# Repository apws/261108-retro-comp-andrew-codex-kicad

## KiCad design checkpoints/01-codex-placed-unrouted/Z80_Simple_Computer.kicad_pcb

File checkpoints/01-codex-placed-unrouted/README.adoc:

= Codex placed, unrouted checkpoint

Preserve these files as the common input for routing comparisons. `checkpoint.json` records their hashes. Open `Z80_Simple_Computer.kicad_pro` to inspect the native snapshot. Signal routing is absent; two inner power planes are filled. Do not edit this checkpoint; copy it into the chosen experiment first.

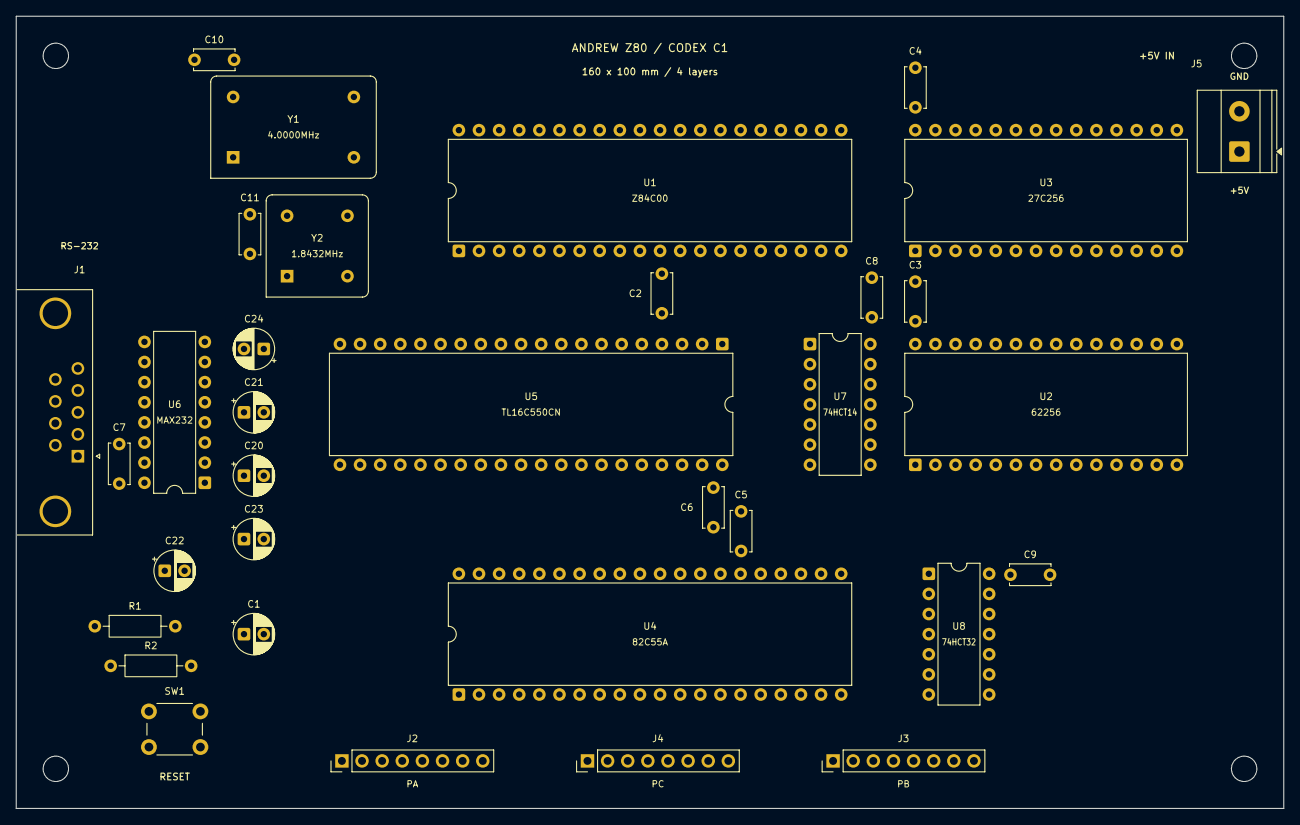
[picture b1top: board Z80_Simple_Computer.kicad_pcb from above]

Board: 4 copper layers, 160.0 x 100.0 mm, 38 parts (0 on the bottom side), 81 nets, no tracks yet.

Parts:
C1: 1uF / 16V; CP_Radial_D5.0mm_P2.50mm
C2, C3, C4, C5, C6, C7, C8, C9, C10, C11: 100nF; C_Disc_D5.0mm_W2.5mm_P5.00mm
C20, C21, C22, C23, C24: 1uF / 25V; CP_Radial_D5.0mm_P2.50mm
H1, H2, H3, H4: M3; MountingHole_3.2mm_M3
J1: RS-232 (DTE pins); DSUB-9_Socket_Horizontal_P2.77x2.84mm_EdgePinOffset4.94mm_H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
J2: PA; PinHeader_1x08_P2.54mm_Vertical
J3: PB; PinHeader_1x08_P2.54mm_Vertical
J4: PC; PinHeader_1x08_P2.54mm_Vertical
J5: +5V INPUT; TerminalBlock_Phoenix_MKDS-1,5-2-5.08_1x02_P5.08mm_Horizont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
R1: 10k; R_Axial_DIN0207_L6.3mm_D2.5mm_P10.16mm_Horizontal
R2: 10; R_Axial_DIN0207_L6.3mm_D2.5mm_P10.16mm_Horizontal
SW1: RESET; SW_PUSH_6mm
U1: Z84C00; DIP-40_W15.24mm
U2: 62256; DIP-28_W15.24mm
U3: 27C256; DIP-28_W15.24mm
U4: 82C55A; DIP-40_W15.24mm
U5: TL16C550CN; DIP-40_W15.24mm
U6: MAX232; DIP-16_W7.62mm
U7: 74HCT14; DIP-14_W7.62mm
U8: 74HCT32; DIP-14_W7.62mm
Y1: 4.0000MHz; Oscillator_DIP-14
Y2: 1.8432MHz; Oscillator_DIP-8

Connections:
+5V: C2.1, C3.1, C4.1, C5.1, C6.1, C7.1, C8.1, C9.1, C10.1, C11.1, C22.1, J5.1, R1.1, U1.11 (V_{CC}), U1.16 (~INT), U1.17 (~NMI), U1.24 (~WAIT), U1.25 (~BUSREQ), U2.28 (VCC), U3.1 (VPP), U3.28 (VCC), U4.26 (VCC), U5.12 (CS0), U5.13 (CS1), U5.38 (~DCD), U5.39 (~RI), U5.40 (VCC), U6.16 (VCC), U7.14 (VCC), U8.14 (VCC), Y1.1 (EN), Y1.14 (Vcc), Y2.1 (EN), Y2.8 (Vcc)
/A0: U1.30 (A_{0}), U2.10 (A0), U3.10 (A0), U4.9 (A0), U5.28 (A0)
/A1: U1.31 (A_{1}), U2.9 (A1), U3.9 (A1), U4.8 (A1), U5.27 (A1)
/A2: U1.32 (A_{2}), U2.8 (A2), U3.8 (A2), U5.26 (A2)
/A3: U1.33 (A_{3}), U2.7 (A3), U3.7 (A3)
/A4: U1.34 (A_{4}), U2.6 (A4), U3.6 (A4)
/A5: U1.35 (A_{5}), U2.5 (A5), U3.5 (A5)
/A6: U1.36 (A_{6}), U2.4 (A6), U3.4 (A6)
/A7: U1.37 (A_{7}), U2.3 (A7), U3.3 (A7), U7.5, U8.2
/A8: U1.38 (A_{8}), U2.25 (A8), U3.25 (A8)
/A9: U1.39 (A_{9}), U2.24 (A9), U3.24 (A9)
/A10: U1.40 (A_{10}), U2.21 (A10), U3.21 (A10)
/A11: U1.1 (A_{11}), U2.23 (A11), U3.23 (A11)
/A12: U1.2 (A_{12}), U2.2 (A12), U3.2 (A12)
/A13: U1.3 (A_{13}), U2.26 (A13), U3.26 (A13)
/A14: U1.4 (A_{14}), U2.1 (A14), U3.27 (A14)
/A15: U1.5 (A_{15}), U7.9, U8.10
/BAUDOUT: U5.9 (RCLK), U5.15 (~BAUDOUT)
/C1M: C20.2, U6.3 (C1-)
/C1P: C20.1, U6.1 (C1+)
/C2M: C21.2, U6.5 (C2-)
/C2P: C21.1, U6.4 (C2+)
/CLK: U1.6 (CLK), Y1.8 (OUT)
/CLK_UART: U5.16 (XIN), Y2.5 (OUT)
/D0: U1.14 (D_{0}), U2.11 (Q0), U3.11 (D0), U4.34 (D0), U5.1 (D0)
/D1: U1.15 (D_{1}), U2.12 (Q1), U3.12 (D1), U4.33 (D1), U5.2 (D1)
/D2: U1.12 (D_{2}), U2.13 (Q2), U3.13 (D2), U4.32 (D2), U5.3 (D2)
/D3: U1.8 (D_{3}), U2.15 (Q3), U3.15 (D3), U4.31 (D3), U5.4 (D3)
/D4: U1.7 (D_{4}), U2.16 (Q4), U3.16 (D4), U4.30 (D4), U5.5 (D4)
/D5: U1.9 (D_{5}), U2.17 (Q5), U3.17 (D5), U4.29 (D5), U5.6 (D5)
/D6: U1.10 (D_{6}), U2.18 (Q6), U3.18 (D6), U4.28 (D6), U5.7 (D6)
/D7: U1.13 (D_{7}), U2.19 (Q7), U3.19 (D7), U4.27 (D7), U5.8 (D7)
/DSR_RS232: J1.6, U6.8 (R2IN)
/DSR_TTL: U5.37 (~DSR), U6.9 (R2OUT)
/DTR_RS232: J1.4, U6.7 (T2OUT)
/DTR_TTL: U5.33 (~DTR), U6.10 (T2IN)
/PA0: J2.1, U4.4 (PA0)
/PA1: J2.2, U4.3 (PA1)
/PA2: J2.3, U4.2 (PA2)
/PA3: J2.4, U4.1 (PA3)
/PA4: J2.5, U4.40 (PA4)
/PA5: J2.6, U4.39 (PA5)
/PA6: J2.7, U4.38 (PA6)
/PA7: J2.8, U4.37 (PA7)
/PB0: J3.1, U4.18 (PB0)
/PB1: J3.2, U4.19 (PB1)
/PB2: J3.3, U4.20 (PB2)
/PB3: J3.4, U4.21 (PB3)
/PB4: J3.5, U4.22 (PB4)
/PB5: J3.6, U4.23 (PB5)
/PB6: J3.7, U4.24 (PB6)
/PB7: J3.8, U4.25 (PB7)
/PC0: J4.1, U4.14 (PC0)
/PC1: J4.2, U4.15 (PC1)
/PC2: J4.3, U4.16 (PC2)
/PC3: J4.4, U4.17 (PC3)
/PC4: J4.5, U4.13 (PC4)
/PC5: J4.6, U4.12 (PC5)
/PC6: J4.7, U4.11 (PC6)
/PC7: J4.8, U4.10 (PC7)
/RESET_H: U4.35 (RESET), U5.35 (MR), U7.2, U7.3
/RESET_RC: C1.1, R1.2, R2.1, U7.1
/RX_RS232: J1.2, U6.13 (R1IN)
/RX_TTL: U5.10 (SIN), U6.12 (R1OUT)
/SW_RESET: R2.2, SW1.1
/TX_RS232: J1.3, U6.14 (T1OUT)
/TX_TTL: U5.11 (SOUT), U6.11 (T1IN)
/VS_MINUS: C24.2, U6.6 (VS-)
/VS_PLUS: C23.1, U6.2 (VS+)
/~A7: U7.6, U8.5
/~A15: U7.8, U8.13
/~IORQ: U1.20 (~IORQ), U8.1, U8.4
/~MREQ: U1.19 (~MREQ), U8.9, U8.12
/~PIOCS: U4.6 (~CS), U8.3
/~RAMCS: U2.20 (~CS), U8.11
/~RD: U1.21 (~RD), U2.22 (~OE), U3.22 (~OE), U4.5 (~RD), U5.21 (~RD)
/~RESET: U1.26 (~RESET), U7.4
/~ROMCS: U3.20 (~CE), U8.8
/~UARTCS: U5.14 (~CS2), U8.6
/~WR: U1.22 (~WR), U2.27 (~WE), U4.36 (~WR), U5.18 (~WR)
GND: C1.2, C2.2, C3.2, C4.2, C5.2, C6.2, C7.2, C8.2, C9.2, C10.2, C11.2, C22.2, C23.2, C24.1, J1.5, J5.2, SW1.2, U1.29 (GND), U2.14 (GND), U3.14 (GND), U4.7 (GND), U5.19 (WR), U5.20 (GND), U5.22 (RD), U5.25 (~ADS), U5.36 (~CTS), U6.15 (GND), U7.7 (GND), U7.11, U7.13, U8.7 (GND), Y1.7 (GND), Y2.4 (GND)

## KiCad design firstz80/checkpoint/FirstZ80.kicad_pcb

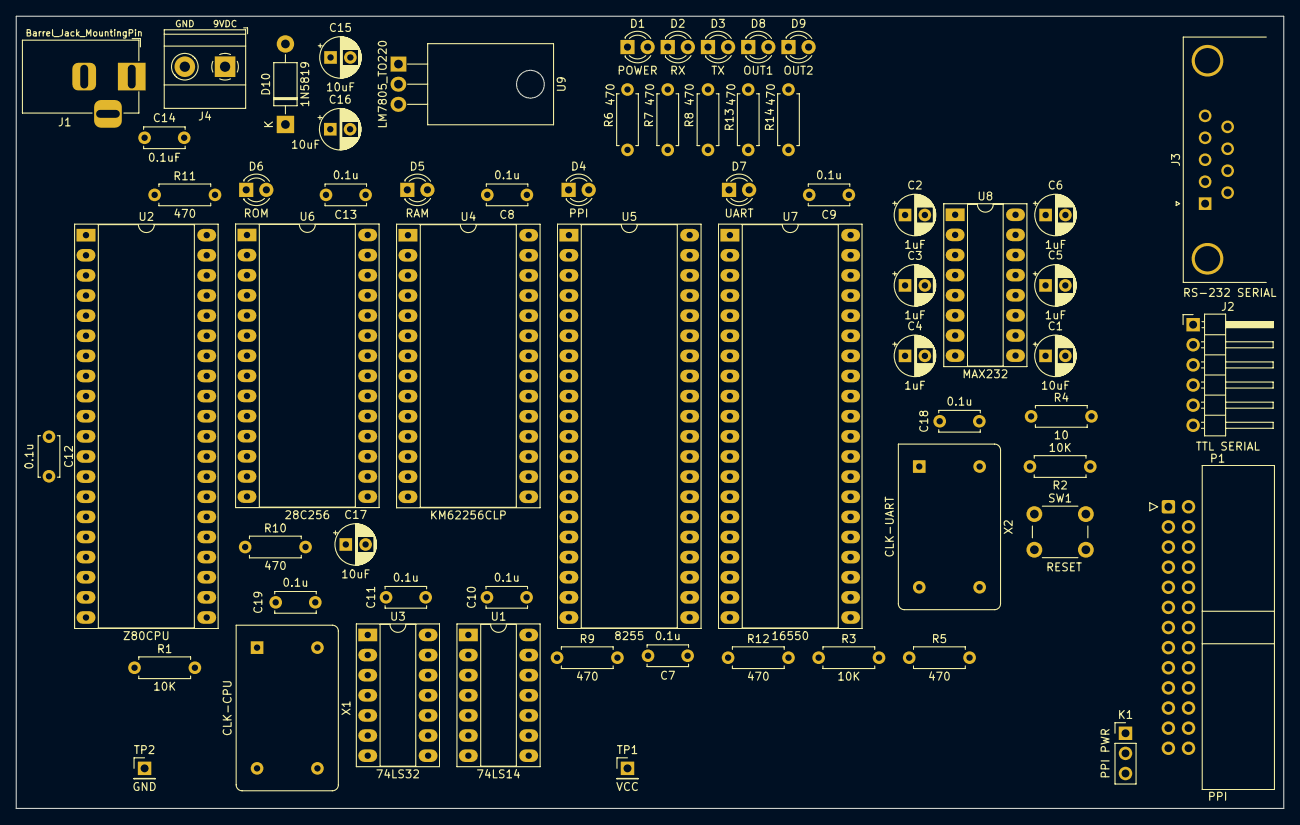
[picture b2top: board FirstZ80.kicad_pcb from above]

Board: 2 copper layers, 160.0 x 100.0 mm, 63 parts (0 on the bottom side), 98 nets, no tracks yet.

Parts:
C1, C15, C16, C17: 10uF; Capacitor_THT__CP_Radial_D5.0mm_P2.50mm
C2, C3, C4, C5, C6: 1uF; Capacitor_THT__CP_Radial_D5.0mm_P2.50mm
C7, C8, C9, C10, C11, C12, C13, C18, C19: 0.1u; Capacitor_THT__C_Disc_D5.0mm_W2.5mm_P5.00mm
C14: 0.1uF; Capacitor_THT__C_Disc_D5.0mm_W2.5mm_P5.00mm
D1: POWER; LED_THT__LED_D3.0mm
D2: RX; LED_THT__LED_D3.0mm
D3: TX; LED_THT__LED_D3.0mm
D4: PPI; LED_THT__LED_D3.0mm
D5: RAM; LED_THT__LED_D3.0mm
D6: ROM; LED_THT__LED_D3.0mm
D7: UART; LED_THT__LED_D3.0mm
D8: OUT1; LED_THT__LED_D3.0mm
D9: OUT2; LED_THT__LED_D3.0mm
D10: 1N5819; Diode_THT__D_DO-41_SOD81_P10.16mm_Horizontal
J1: Barrel_Jack_MountingPin; Connector_BarrelJack__BarrelJack_Horizontal
J2: TTL SERIAL; Connector_PinHeader_2.54mm__PinHeader_1x06_P2.54mm_Horizont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
J3: RS-232 SERIAL; Connector_Dsub__DSUB-9_Male_Horizontal_P2.77x2.84mm_EdgePin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
J4: 9VDC; TerminalBlock_Phoenix__TerminalBlock_Phoenix_MKDS-1,5-2-5.0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
K1: PPI PWR; Connector_PinHeader_2.54mm__PinHeader_1x03_P2.54mm_Vertical
P1: PPI; Connector_IDC__IDC-Header_2x13_P2.54mm_Horizontal
R1, R2, R3: 10K; Resistor_THT__R_Axial_DIN0207_L6.3mm_D2.5mm_P7.62mm_Horizon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
R4: 10; Resistor_THT__R_Axial_DIN0207_L6.3mm_D2.5mm_P7.62mm_Horizon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
R5, R6, R7, R8, R9, R10, R11, R12, R13, R14: 470; Resistor_THT__R_Axial_DIN0207_L6.3mm_D2.5mm_P7.62mm_Horizon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
SW1: RESET; Button_Switch_THT__SW_PUSH_6mm
TP1: VCC; Connector_PinHeader_2.54mm__PinHeader_1x01_P2.54mm_Vertical
TP2: GND; Connector_PinHeader_2.54mm__PinHeader_1x01_P2.54mm_Vertical
U1: 74LS14; Package_DIP__DIP-14_W7.62mm_Socket_LongPads
U2: Z80CPU; Package_DIP__DIP-40_W15.24mm_Socket_LongPads
U3: 74LS32; Package_DIP__DIP-14_W7.62mm_Socket_LongPads
U4: KM62256CLP; Package_DIP__DIP-28_W15.24mm_Socket_LongPads
U5: 8255; Package_DIP__DIP-40_W15.24mm_Socket_LongPads
U6: 28C256; Package_DIP__DIP-28_W15.24mm_Socket_LongPads
U7: 16550; Package_DIP__DIP-40_W15.24mm_Socket_LongPads
U8: MAX232; Package_DIP__DIP-16_W7.62mm_Socket_LongPads
U9: LM7805_TO220; Package_TO_SOT_THT__TO-220-3_Horizontal_TabDown
X1: CLK-CPU; Oscillator__Oscillator_DIP-14
X2: CLK-UART; Oscillator__Oscillator_DIP-14

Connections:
/9VDC: C14.1, D10.2 (A), J1.1, J4.1
/A00: U2.30 (A0), U4.10 (A0), U5.9 (A0), U6.10 (A0), U7.28 (A0)
/A01: U2.31 (A1), U4.9 (A1), U5.8 (A1), U6.9 (A1), U7.27 (A1)
/A02: U2.32 (A2), U4.8 (A2), U6.8 (A2), U7.26 (A2)
/A03: U2.33 (A3), U4.7 (A3), U6.7 (A3)
/A04: U2.34 (A4), U4.6 (A4), U6.6 (A4)
/A05: U2.35 (A5), U4.5 (A5), U6.5 (A5)
/A06: U2.36 (A6), U4.4 (A6), U6.4 (A6)
/A07: U1.5, U2.37 (A7), U3.2, U4.3 (A7), U6.3 (A7)
/A08: U2.38 (A8), U4.25 (A8), U6.25 (A8)
/A09: U2.39 (A9), U4.24 (A9), U6.24 (A9)
/A10: U2.40 (A10), U4.21 (A10), U6.21 (A10)
/A11: U2.1 (A11), U4.23 (A11), U6.23 (A11)
/A12: U2.2 (A12), U4.2 (A12), U6.2 (A12)
/A13: U2.3 (A13), U4.26 (A13), U6.26 (A13)
/A14: U2.4 (A14), U4.1 (A14), U6.1 (A14)
/A15: U1.9, U2.5 (A15), U3.10
/CLK-CPU: U2.6 (~CLK), X1.8 (OUT)
/CLK-UART: U7.16 (XIN), X2.8 (OUT)
/D00: U2.14 (D0), U4.11 (Q0), U5.34 (D0), U6.11 (D0), U7.1 (D0)
/D01: U2.15 (D1), U4.12 (Q1), U5.33 (D1), U6.12 (D1), U7.2 (D1)
/D02: U2.12 (D2), U4.13 (Q2), U5.32 (D2), U6.13 (D2), U7.3 (D2)
/D03: U2.8 (D3), U4.15 (Q3), U5.31 (D3), U6.15 (D3), U7.4 (D3)
/D04: U2.7 (D4), U4.16 (Q4), U5.30 (D4), U6.16 (D4), U7.5 (D4)
/D05: U2.9 (D5), U4.17 (Q5), U5.29 (D5), U6.17 (D5), U7.6 (D5)
/D06: U2.10 (D6), U4.18 (Q6), U5.28 (D6), U6.18 (D6), U7.7 (D6)
/D07: U2.13 (D7), U4.19 (Q7), U5.27 (D7), U6.19 (D7), U7.8 (D7)
/PA0: P1.2, U5.4 (PA0)
/PA1: P1.4, U5.3 (PA1)
/PA2: P1.6, U5.2 (PA2)
/PA3: P1.8, U5.1 (PA3)
/PA4: P1.10, U5.40 (PA4)
/PA5: P1.12, U5.39 (PA5)
/PA6: P1.14, U5.38 (PA6)
/PA7: P1.16, U5.37 (PA7)
/PB0: P1.18, U5.18 (PB0)
/PB1: P1.20, U5.19 (PB1)
/PB2: P1.22, U5.20 (PB2)
/PB3: P1.24, U5.21 (PB3)
/PB4: P1.23, U5.22 (PB4)
/PB5: P1.21, U5.23 (PB5)
/PB6: P1.19, U5.24 (PB6)
/PB7: P1.17, U5.25 (PB7)
/PC0: P1.1, U5.14 (PC0)
/PC1: P1.3, U5.15 (PC1)
/PC2: P1.5, U5.16 (PC2)
/PC3: P1.7, U5.17 (PC3)
/PC4: P1.9, U5.13 (PC4)
/PC5: P1.11, U5.12 (PC5)
/PC6: P1.13, U5.11 (PC6)
/PC7: P1.15, U5.10 (PC7)
/RESET: U1.2, U1.3, U5.35 (RESET), U7.35 (MR)
/RX: J3.2, U8.8 (R2IN)
/RX-TTL: J2.4, R7.2, U7.10 (SIN), U8.9 (R2OUT)
/TX: J3.3, U8.7 (T2OUT)
/TX-TTL: J2.5, R8.2, U7.11 (SOUT), U8.10 (T2IN)
/VCC_PP: K1.2, P1.25
/VI: C15.1, D10.1 (K), U9.1 (VI)
/~CS-PPI: R9.2, U3.3, U5.6 (~CS)
/~CS-RAM: R10.2, U3.11, U4.20 (~CS)
/~CS-ROM: R11.2, U3.8, U6.22 (~OE)
/~CS-UART: R12.2, U3.6, U7.14 (~CS2)
/~CTS-TTL: J2.6, U7.36 (~CTS), U8.12 (R1OUT)
/~CTS: J3.8, U8.13 (R1IN)
/~IORQ: U2.20 (~IORQ), U3.1, U3.4
/~MREQ: U2.19 (~MREQ), U3.9, U3.12
/~OUT1: R13.2, U7.34 (~OUT1)
/~OUT2: R14.2, U7.31 (~OUT2)
/~RD: U2.21 (~RD), U4.22 (~OE), U5.5 (~RD), U6.20 (~CS), U7.21 (~RD)
/~RESET: U1.4, U2.26 (~RESET)
/~RTS-TTL: J2.2, U7.32 (~RTS), U8.11 (T1IN)
/~RTS: J3.7, U8.14 (T1OUT)
/~WR: U2.22 (~WR), U4.27 (~WE), U5.36 (~WR), U6.27 (~WE), U7.18 (~WR)
GND: C1.2, C4.1, C6.2, C7.2, C8.2, C9.2, C10.2, C11.2, C12.2, C13.2, C14.2, C15.2, C16.2, C17.2, C18.2, C19.2, J1.2, J1.MP (MountPin), J2.1, J3.0 (PAD), J3.5, J4.2, K1.1, P1.26, R5.2, R6.2, SW1.2, TP2.1, U1.7 (GND), U2.29 (GND), U3.7 (GND), U4.14 (GND), U5.7 (GND), U6.14 (GND), U7.19 (WR), U7.20 (GND), U7.22 (RD), U7.25 (~ADS), U8.15 (GND), U9.2 (GND), X1.7 (GND), X2.7 (GND)
unnamed: C1.1, R2.2, R4.1, U1.1
unnamed: D1.1 (K), R6.1
unnamed: D2.1 (K), R7.1
unnamed: D3.1 (K), R8.1
unnamed: D4.1 (K), R9.1
unnamed: D5.1 (K), R10.1
unnamed: D6.1 (K), R11.1
unnamed: D7.1 (K), R12.1
unnamed: D8.1 (K), R13.1
unnamed: D9.1 (K), R14.1
unnamed: R4.2, SW1.1
unnamed: U1.6, U3.5
unnamed: U1.8, U3.13
unnamed: R1.2, U2.16 (~INT), U2.17 (~NMI), U2.23 (~BUSACK), U2.24 (~WAIT)
unnamed: R3.2, U7.12 (CS0), U7.13 (CS1), U7.39 (~RI)
unnamed: U7.9 (RCLK), U7.15 (~BAUDOUT)
unnamed: R5.1, U7.37 (~DSR), U7.38 (~DCD)
unnamed: C2.1, U8.1 (C1+)
unnamed: C2.2, U8.3 (C1-)
unnamed: C3.1, U8.4 (C2+)
unnamed: C3.2, U8.5 (C2-)
unnamed: C5.1, U8.2 (VS+)
unnamed: C4.2, U8.6 (VS-)
VCC: C5.2, C6.1, C7.1, C8.1, C9.1, C10.1, C11.1, C12.1, C13.1, C16.1, C17.1, C18.1, C19.1, D1.2 (A), D2.2 (A), D3.2 (A), D4.2 (A), D5.2 (A), D6.2 (A), D7.2 (A), D8.2 (A), D9.2 (A), J2.3, K1.3, R1.1, R2.1, R3.1, TP1.1, U1.14 (VCC), U2.11 (VCC), U3.14 (VCC), U4.28 (VCC), U5.26 (VCC), U6.28 (VCC), U7.40 (VCC), U8.16 (VCC), U9.3 (VO), X1.14 (Vcc), X2.14 (Vcc)
